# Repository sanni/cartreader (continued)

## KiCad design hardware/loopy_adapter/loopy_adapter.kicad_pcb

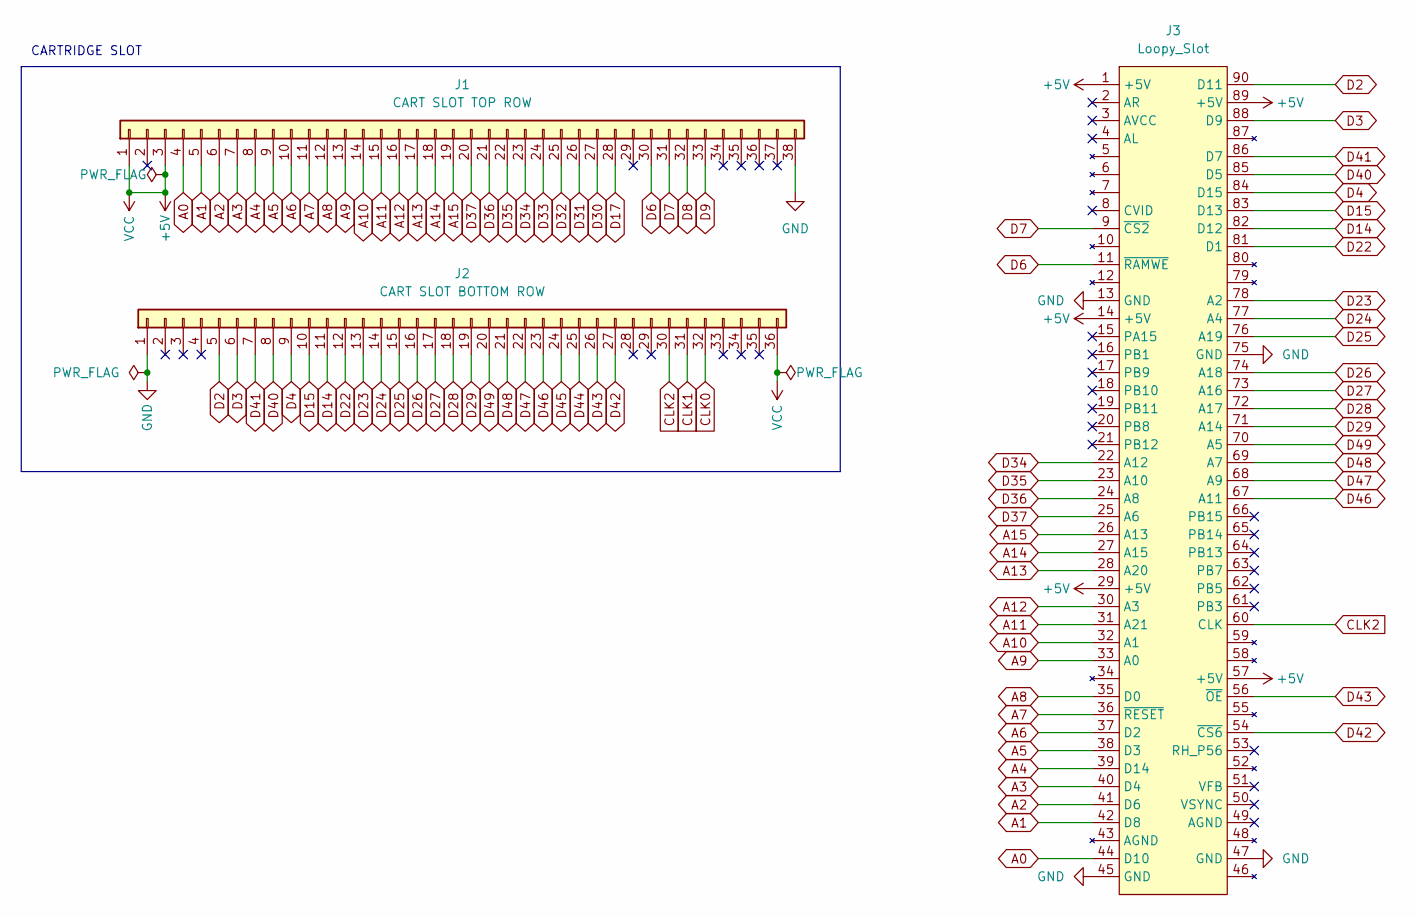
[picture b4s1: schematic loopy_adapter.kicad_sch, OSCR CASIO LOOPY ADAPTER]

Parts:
J1: CART SLOT TOP ROW; PinSocket_1x38_P2.54mm_Vertical
J2: CART SLOT BOTTOM ROW; PinSocket_1x36_P2.54mm_Vertical
J3: Loopy_Slot

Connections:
+5V: J1.1, J1.3, J2.36, J3.1 (+5V), J3.14 (+5V), J3.29 (+5V), J3.57 (+5V), J3.89 (+5V)
A0: J1.4, J3.44 (D10)
A1: J1.5, J3.42 (D8)
A2: J1.6, J3.41 (D6)
A3: J1.7, J3.40 (D4)
A4: J1.8, J3.39 (D14)
A5: J1.9, J3.38 (D3)
A6: J1.10, J3.37 (D2)
A7: J1.11, J3.36 (~RESET)
A8: J1.12, J3.35 (D0)
A9: J1.13, J3.33 (A0)
A10: J1.14, J3.32 (A1)
A11: J1.15, J3.31 (A21)
A12: J1.16, J3.30 (A3)
A13: J1.17, J3.28 (A20)
A14: J1.18, J3.27 (A15)
A15: J1.19, J3.26 (A13)
CLK0: J2.32
CLK1: J2.31
CLK2: J2.30, J3.60 (CLK)
D2: J2.5, J3.90 (D11)
D3: J2.6, J3.88 (D9)
D4: J2.9, J3.84 (D15)
D6: J1.30, J3.11 (~RAMWE)
D7: J1.31, J3.9 (~CS2)
D8: J1.32
D9: J1.33
D14: J2.11, J3.82 (D12)
D15: J2.10, J3.83 (D13)
D17: J1.28
D22: J2.12, J3.81 (D1)
D23: J2.13, J3.78 (A2)
D24: J2.14, J3.77 (A4)
D25: J2.15, J3.76 (A19)
D26: J2.16, J3.74 (A18)
D27: J2.17, J3.73 (A16)
D28: J2.18, J3.72 (A17)
D29: J2.19, J3.71 (A14)
D30: J1.27
D31: J1.26
D32: J1.25
D33: J1.24
D34: J1.23, J3.22 (A12)
D35: J1.22, J3.23 (A10)
D36: J1.21, J3.24 (A8)
D37: J1.20, J3.25 (A6)
D40: J2.8, J3.85 (D5)
D41: J2.7, J3.86 (D7)
D42: J2.27, J3.54 (~CS6)
D43: J2.26, J3.56 (~OE)
D44: J2.25
D45: J2.24
D46: J2.23, J3.67 (A11)
D47: J2.22, J3.68 (A9)
D48: J2.21, J3.69 (A7)
D49: J2.20, J3.70 (A5)
GND: J1.38, J2.1, J3.13 (GND), J3.45 (GND), J3.47 (GND), J3.75 (GND)

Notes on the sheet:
CARTRIDGE SLOT

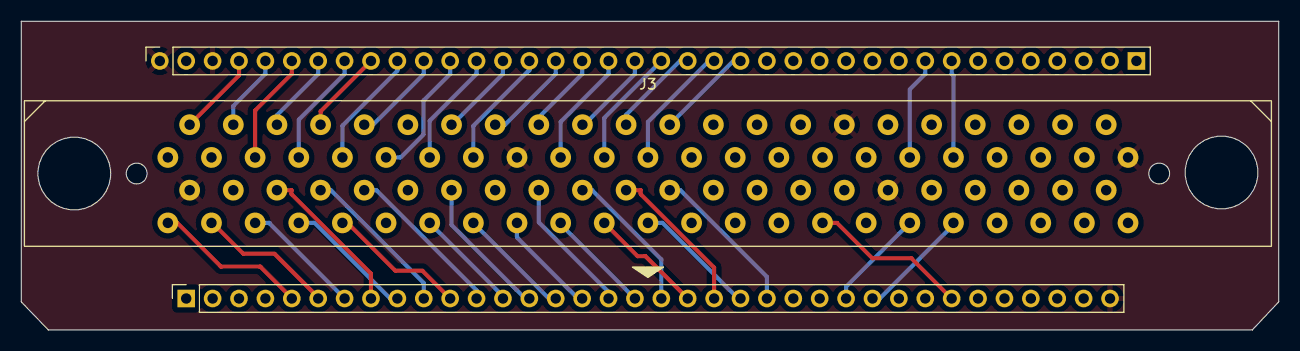
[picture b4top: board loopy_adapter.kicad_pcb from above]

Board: 2 copper layers, 121.0 x 29.7 mm, 3 parts (0 on the bottom side), 46 nets.

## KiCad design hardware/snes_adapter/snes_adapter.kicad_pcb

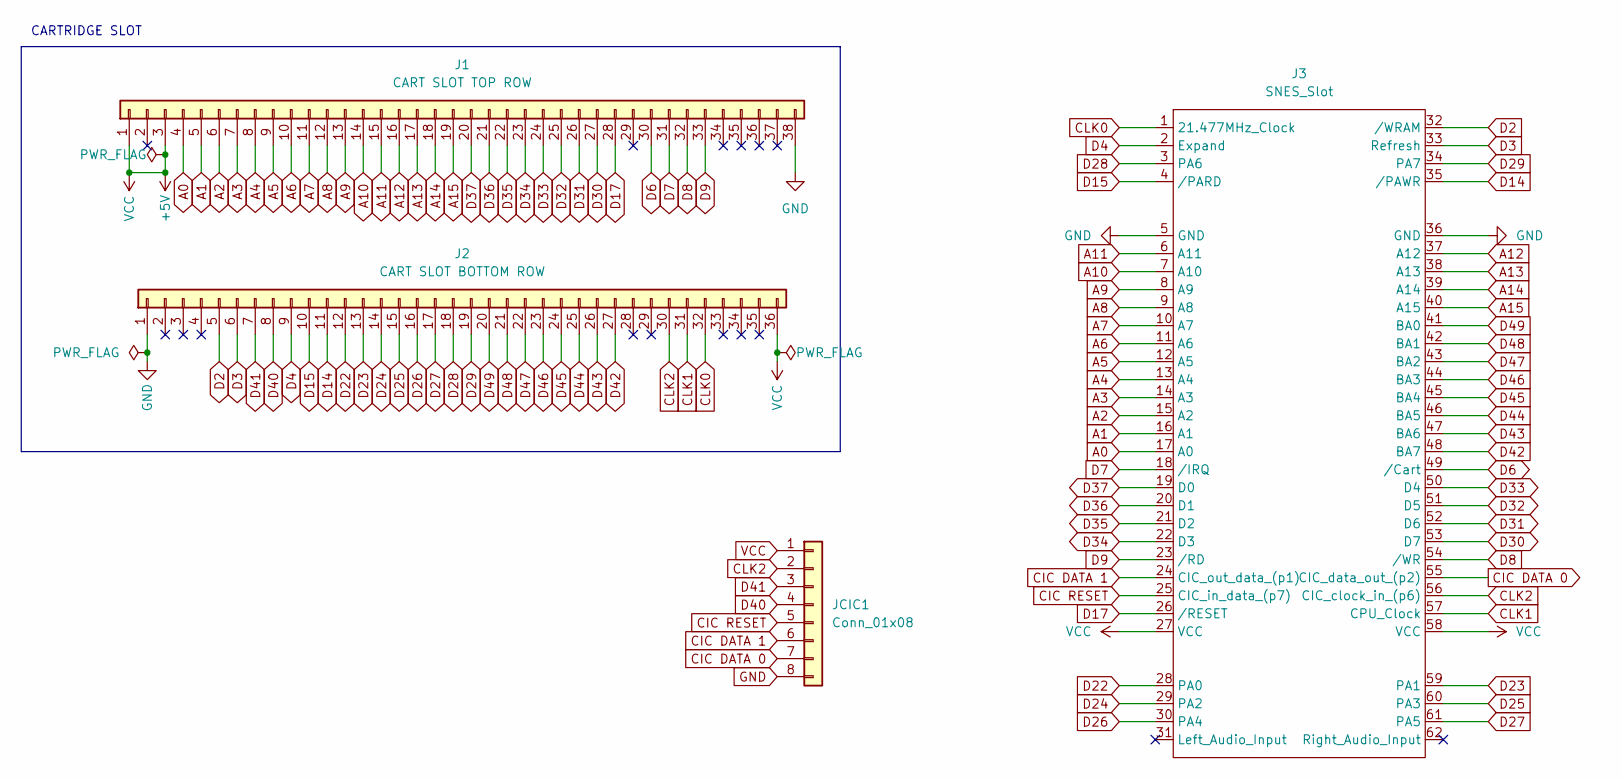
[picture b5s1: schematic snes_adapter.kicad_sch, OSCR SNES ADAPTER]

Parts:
J1: CART SLOT TOP ROW; PinSocket_1x38_P2.54mm_Vertical
J2: CART SLOT BOTTOM ROW; PinSocket_1x36_P2.54mm_Vertical
J3: SNES_Slot
JCIC1: Conn_01x08

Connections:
A0: J1.4, J3.17 (A0)
A1: J1.5, J3.16 (A1)
A2: J1.6, J3.15 (A2)
A3: J1.7, J3.14 (A3)
A4: J1.8, J3.13 (A4)
A5: J1.9, J3.12 (A5)
A6: J1.10, J3.11 (A6)
A7: J1.11, J3.10 (A7)
A8: J1.12, J3.9 (A8)
A9: J1.13, J3.8 (A9)
A10: J1.14, J3.7 (A10)
A11: J1.15, J3.6 (A11)
A12: J1.16, J3.37 (A12)
A13: J1.17, J3.38 (A13)
A14: J1.18, J3.39 (A14)
A15: J1.19, J3.40 (A15)
CIC DATA 0: J3.55 (CIC_data_out_(p2)), JCIC1.7
CIC DATA 1: J3.24 (CIC_out_data_(p1)), JCIC1.6
CIC RESET: J3.25 (CIC_in_data_(p7)), JCIC1.5
CLK0: J2.32, J3.1 (21.477MHz_Clock)
CLK1: J2.31, J3.57 (CPU_Clock)
CLK2: J2.30, J3.56 (CIC_clock_in_(p6)), JCIC1.2
D2: J2.5, J3.32 (/WRAM)
D3: J2.6, J3.33 (Refresh)
D4: J2.9, J3.2 (Expand)
D6: J1.30, J3.49 (/Cart)
D7: J1.31, J3.18 (/IRQ)
D8: J1.32, J3.54 (/WR)
D9: J1.33, J3.23 (/RD)
D14: J2.11, J3.35 (/PAWR)
D15: J2.10, J3.4 (/PARD)
D17: J1.28, J3.26 (/RESET)
D22: J2.12, J3.28 (PA0)
D23: J2.13, J3.59 (PA1)
D24: J2.14, J3.29 (PA2)
D25: J2.15, J3.60 (PA3)
D26: J2.16, J3.30 (PA4)
D27: J2.17, J3.61 (PA5)
D28: J2.18, J3.3 (PA6)
D29: J2.19, J3.34 (PA7)
D30: J1.27, J3.53 (D7)
D31: J1.26, J3.52 (D6)
D32: J1.25, J3.51 (D5)
D33: J1.24, J3.50 (D4)
D34: J1.23, J3.22 (D3)
D35: J1.22, J3.21 (D2)
D36: J1.21, J3.20 (D1)
D37: J1.20, J3.19 (D0)
D40: J2.8, JCIC1.4
D41: J2.7, JCIC1.3
D42: J2.27, J3.48 (BA7)
D43: J2.26, J3.47 (BA6)
D44: J2.25, J3.46 (BA5)
D45: J2.24, J3.45 (BA4)
D46: J2.23, J3.44 (BA3)
D47: J2.22, J3.43 (BA2)
D48: J2.21, J3.42 (BA1)
D49: J2.20, J3.41 (BA0)
GND: J1.38, J2.1, J3.5 (GND), J3.36 (GND), JCIC1.8
VCC: J1.1, J1.3, J2.36, J3.27 (VCC), J3.58 (VCC), JCIC1.1

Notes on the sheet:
CARTRIDGE SLOT

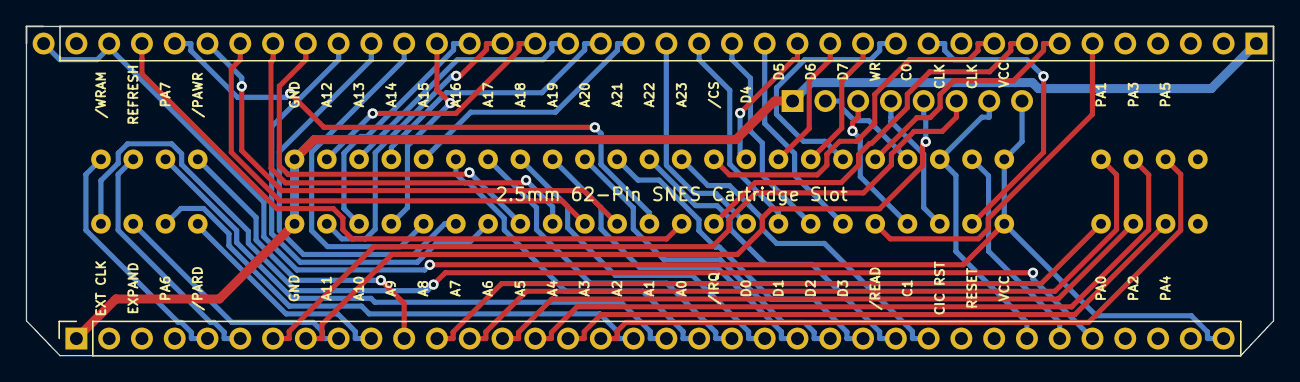
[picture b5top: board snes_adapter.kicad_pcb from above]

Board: 2 copper layers, 96.6 x 25.5 mm, 4 parts (1 on the bottom side), 60 nets.

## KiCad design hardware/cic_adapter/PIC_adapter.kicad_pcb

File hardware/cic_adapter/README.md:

### Important: The CIC adapters are completely untested and still a work-in-progress, so the PCB files might contain errors or not work at all.    

##

The D411_F411_adapter is for using the original CIC chip either out of a cartridge(D411) or out of a SNES console(F411). They will be region locked and you can only dump SA1 games from the region of the CIC chip. Furthermore it has not been tested if this works at all, so right now it's just an unproven idea to save people the trouble of programming a PIC microcontroller.    

##

The PIC_adapter is for using either the PIC12F629 DIP or SMD(flashed with snescic-lock-resync.hex) or PIC16F630 DIP(flashed with supercic-lock_p16f630.hex) microcontrollers. They are region-free so they can dump SA1 cartridges from any country.     

Hexfiles:     
- [snescic-lock-resync.hex](https://github.com/mrehkopf/sd2snes/tree/develop/cic)    
- [supercic-lock_p16f630.hex](https://sd2snes.de/blog/cool-stuff/supercic)      

More Info:   
- [Flashing the snesCIC](https://github.com/sanni/cartreader/wiki/Flashing-the-snesCIC)

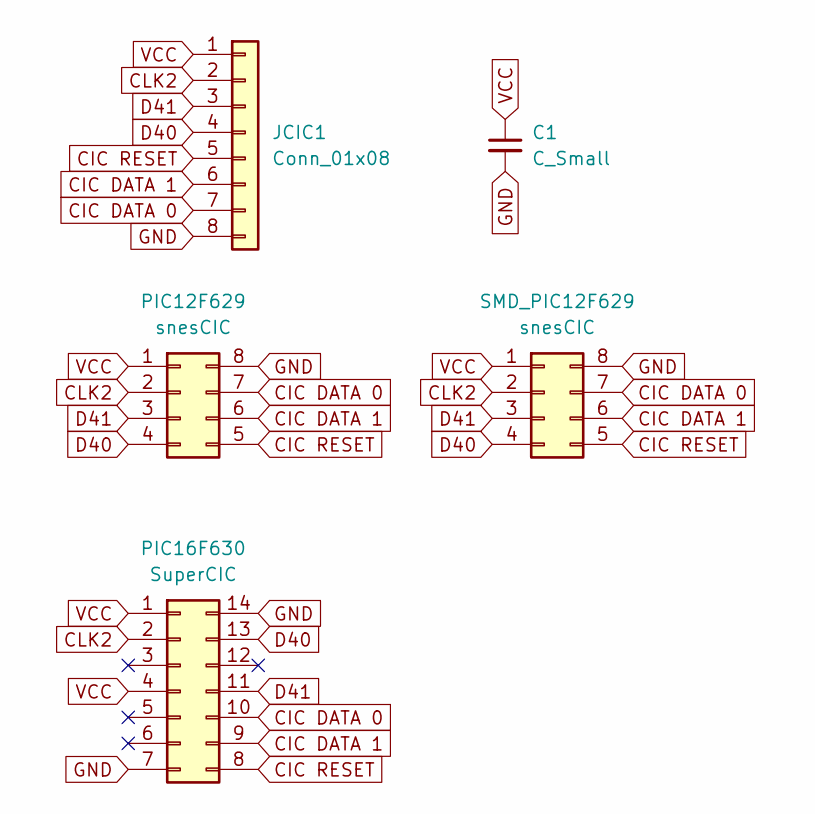
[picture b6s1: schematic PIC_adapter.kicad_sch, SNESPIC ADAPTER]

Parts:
C1: C_Small
JCIC1: Conn_01x08
PIC12F629: snesCIC
PIC16F630: SuperCIC
SMD_PIC12F629: snesCIC

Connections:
CIC DATA 0: JCIC1.7, PIC12F629.7, PIC16F630.10, SMD_PIC12F629.7
CIC DATA 1: JCIC1.6, PIC12F629.6, PIC16F630.9, SMD_PIC12F629.6
CIC RESET: JCIC1.5, PIC12F629.5, PIC16F630.8, SMD_PIC12F629.5
CLK2: JCIC1.2, PIC12F629.2, PIC16F630.2, SMD_PIC12F629.2
D40: JCIC1.4, PIC12F629.4, PIC16F630.13, SMD_PIC12F629.4
D41: JCIC1.3, PIC12F629.3, PIC16F630.11, SMD_PIC12F629.3
GND: C1.2, JCIC1.8, PIC12F629.8, PIC16F630.7, PIC16F630.14, SMD_PIC12F629.8
VCC: C1.1, JCIC1.1, PIC12F629.1, PIC16F630.1, PIC16F630.4, SMD_PIC12F629.1

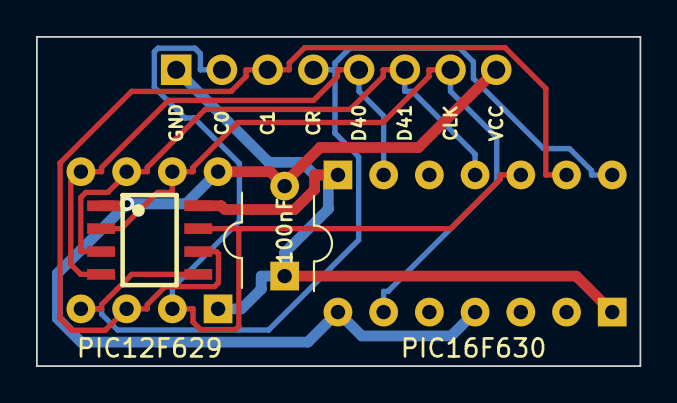
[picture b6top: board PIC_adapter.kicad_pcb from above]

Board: 2 copper layers, 33.5 x 18.3 mm, 5 parts (1 on the bottom side), 8 nets.

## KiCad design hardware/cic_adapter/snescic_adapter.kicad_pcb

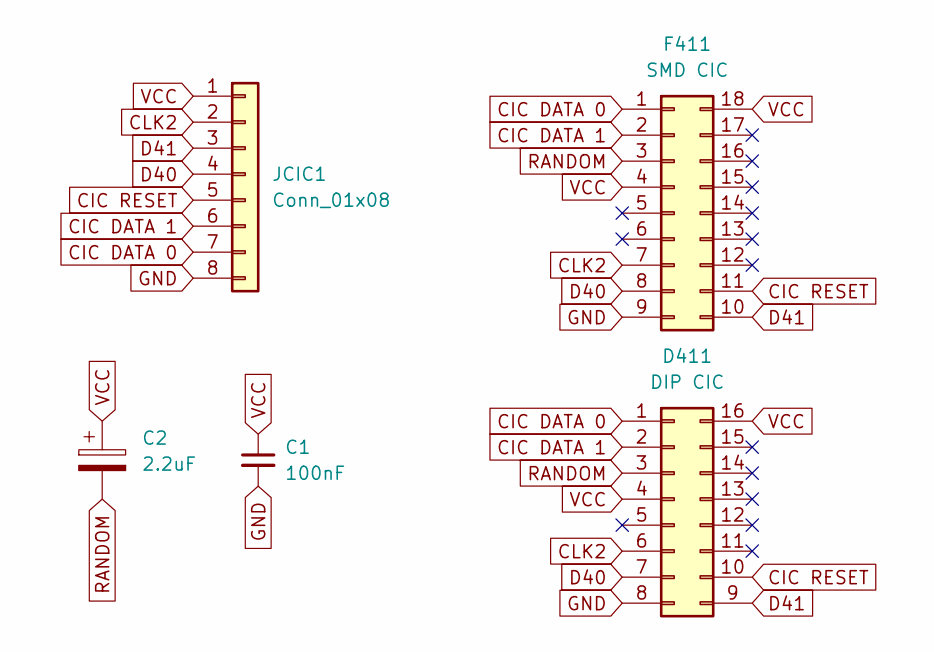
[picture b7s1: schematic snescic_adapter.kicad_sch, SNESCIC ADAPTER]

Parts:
C1: 100nF
C2: 2.2uF
D411: DIP CIC
F411: SMD CIC
JCIC1: Conn_01x08

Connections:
CIC DATA 0: D411.1, F411.1, JCIC1.7
CIC DATA 1: D411.2, F411.2, JCIC1.6
CIC RESET: D411.10, F411.11, JCIC1.5
CLK2: D411.6, F411.7, JCIC1.2
D40: D411.7, F411.8, JCIC1.4
D41: D411.9, F411.10, JCIC1.3
GND: C1.2, D411.8, F411.9, JCIC1.8
RANDOM: C2.2, D411.3, F411.3
VCC: C1.1, C2.1, D411.4, D411.16, F411.4, F411.18, JCIC1.1

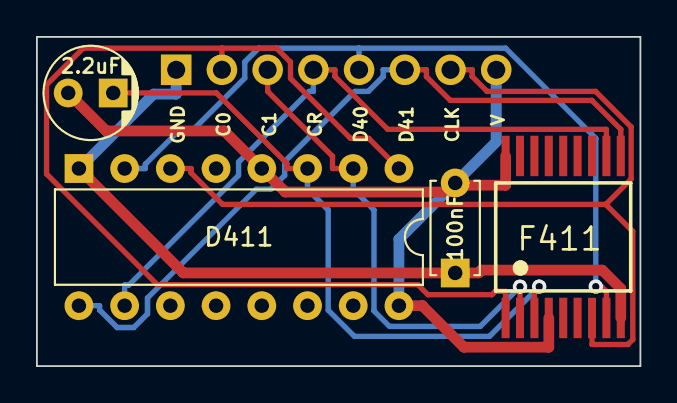
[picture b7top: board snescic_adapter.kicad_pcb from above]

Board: 2 copper layers, 33.5 x 18.3 mm, 5 parts (1 on the bottom side), 9 nets.

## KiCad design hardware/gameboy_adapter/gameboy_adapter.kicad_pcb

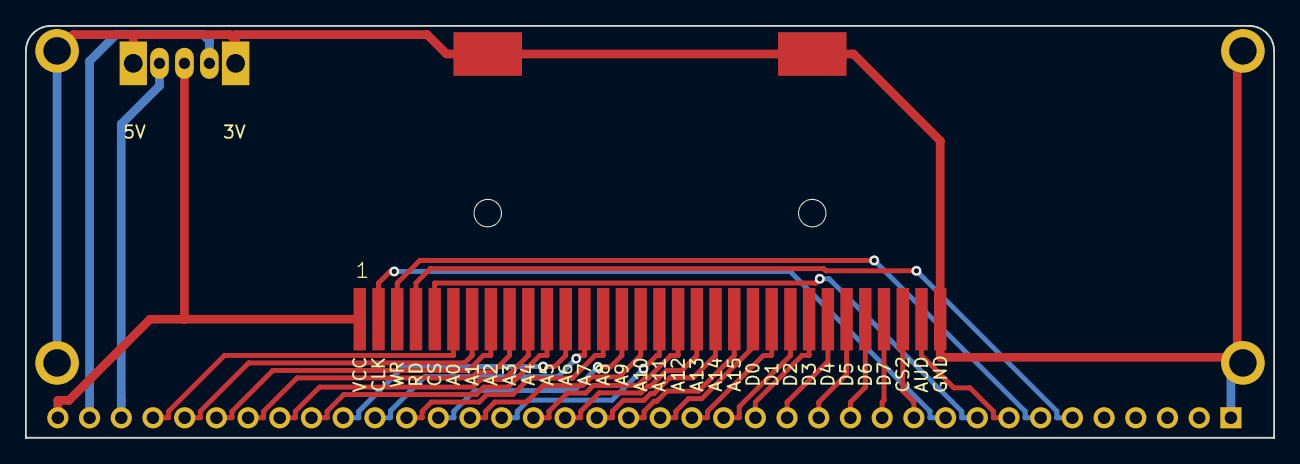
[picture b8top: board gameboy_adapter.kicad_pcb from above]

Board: 2 copper layers, 100.0 x 33.0 mm, 7 parts (0 on the bottom side), 34 nets.

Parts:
J1: CART SLOT TOP ROW; PinSocket_1x38_P2.54mm_Vertical
J2: GBA_Slot; GBA-SLOT-B
M2_1, M2_2, M2_3, M2_10: Screw_Terminal_01x01; MountingHole_2.2mm_M2_ISO7380_Pad
SW1: SW_SPDT; SW_CuK_OS102011MA1QN1_SPDT_Angled

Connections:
+3V3: J1.2, SW1.1 (A)
+5V: J1.3, SW1.3 (C)
A0: J1.4, J2.6 (AD0)
A1: J1.5, J2.7 (AD1)
A2: J1.6, J2.8 (AD2)
A3: J1.7, J2.9 (AD3)
A4: J1.8, J2.10 (AD4)
A5: J1.9, J2.11 (AD5)
A6: J1.10, J2.12 (AD6)
A7: J1.11, J2.13 (AD7)
A8: J1.12, J2.14 (AD8)
A9: J1.13, J2.15 (AD9)
A10: J1.14, J2.16 (AD10)
A11: J1.15, J2.17 (AD11)
A12: J1.16, J2.18 (AD12)
A13: J1.17, J2.19 (AD13)
A14: J1.18, J2.20 (AD14)
A15: J1.19, J2.21 (AD15)
D6: J1.30, J2.5 (CS1)
D7: J1.31, J2.31 (AUD_IRQ)
D8: J1.32, J2.3 (WR)
D9: J1.33, J2.4 (RD)
D16: J1.29, J2.2 (CLK)
D17: J1.28, J2.30 (RST_CS2)
D30: J1.27, J2.29 (D7_A23)
D31: J1.26, J2.28 (D6_A22)
D32: J1.25, J2.27 (D5_A21)
D33: J1.24, J2.26 (D4_A20)
D34: J1.23, J2.25 (D3_A19)
D35: J1.22, J2.24 (D2_A18)
D36: J1.21, J2.23 (D1_A17)
D37: J1.20, J2.22 (D0_A16)
GND: J1.38, J2.32 (GND), J2.SHIELD_3, J2.SHIELD_4, M2_1.1, M2_2.1, M2_3.1, M2_10.1
VCC: J1.1, J2.1 (VCC), SW1.2 (B)

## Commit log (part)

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2024-04-22 remove some duplicate printing code and declare more global text strings
2024-04-24 replace cart select code with code used in NES, COLV, INTV
2024-04-27 replace 2600 cart selection code with code used in NES, COLV & INTV
2024-04-27 Update c64cart.txt
    Updated to work with C64.ino that fixes Issue #902
2024-04-28 replace C64 cart selection code with code used in NES, COLV & INTV
2024-04-28 fix ordering in 7800.txt
2024-04-28 fix formatting of newly added documentation
2024-04-29 add 5200 and arccart section to README.md
2024-05-01 replace FAIRCHILD, ODY2, MSX and VECTREX cart selection code with code used in NES, COLV & INTV. Define "Database not found" in OSCR.cpp
2024-05-01 remove duplicate CRC printing and calculation function
2024-05-01 remove duplicate code in printing CRC
2024-05-03 remove duplicate string literals
2024-05-03 fix signed/unsigned warning
2024-05-03 Add support for mapper 3E, 32K ROM 32K RAM Tigervision
2024-05-07 fix 2600 mapper selection for Serial
2024-05-07 Fixed (added) missing FS() macro on some FSTRING constants
    This was causing two symptoms/bugs:
    * OSCR_LOG.txt was being spammed with random data.
    * The size of OSCR_LOG.txt would get so big that copying the log would take a long time, possibly minutes. Oftentimes this caused the display to appear to hang after searching for the CRC (after "->"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
    If using the global log and a version of master since e61ac414d89556c941f0b8ca76e5d7d6684037f0 you should delete OSCR_LOG.txt from your SD card as it will likely be very large and continue to cause d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
2024-05-10 add serial printing to print instructions
2024-05-11 define "File doesn't exist" in OSCR.cpp/h
2024-05-12 reduce duplicate code by parameterise ROML/ROMH
2024-05-12 remove duplicate code for 2600 3E & 3F mapper
2024-05-12 use constant for "Saving to" instead declare the string several times
2024-05-20 remove duplicate code to open file for verfication
2024-05-20 remove duplicate code to write Flash Command
2024-05-24 support mapper > 255, implement mapper 446 submapper 0&1 - thanks to NewRisingSun for support, fix iNES2.0 mapper parsing of byte 8
2024-05-25 add option to clear display and remove duplicate code
2024-05-26 add common function to open create folder, print message and open file. Remove duplicate code
2024-05-28 define more commonly used string in OSCR and reuse them
2024-05-30 reuse code to write NES maker command
2024-05-30 reuse n64 flashrom Xplorer command sequence
2024-06-02 Add checks for unsafe configurations
    * Fixes #929
    * Updated `ci.yml` to define `GITHUB_CI`
    * Compilation will now error if VSELECT is enabled on hardware versions that don't support it (any version other than HW5).
    * HW4 and SERIAL might work but are untested. The error message for these versions reflects this.
    * Erroring when unsafe configurations are defined can be overridden by defining `ALLOW_UNSAFE_CONFIG` which will throw a warning instead.
    * This should only be done if trying to implement or test on a currently unsupported platform.
2024-06-03 reuse command sequence for GB
2024-06-10 Fix compilation errors when the FLASH core is enabled without FLASH16
    Commit References:
    * a32c6b3bfff066b04d81faea0e578b80cb4a3108 - Added ATTENTION_3_3V flash string but placed the definition inside a FLASH16 ifdef.
    * 4d000418a8f4e4a29297f83e30922100da7b21f5 - Added use of writeWord_Flash to FLASH8 without removing the FLASH16 ifdef around it.
2024-06-13 Add option to force ROM size for MD carts
2024-06-15 replace duplicate error string "Can't open file"
2024-06-16 define common string "Select file"
2024-06-26 SNES: Add 2x2MB flash to CFI (thx to MouseBiteLabs)
2024-06-27 Fix verifyFlash()
2024-06-29 reuse common string "ROM Size: "
2024-06-29 Disable SRAM when flashing 2x2MB repro
2024-06-30 Cleaning up debug stuff
2024-06-30 Always disable SRAM when flashing any hirom repros
2024-06-30 Fix reading Bahamut Lagoon English Translation SRAM (thx to Cowboyjunkie)
    https://github.com/sanni/cartreader/issues/917
2024-06-30 Alternate fix
2024-07-02 Fix color cycling when idle
2024-07-05 13.5 Fix SFM flash menu
    https://github.com/sanni/cartreader/issues/980
2024-07-07 Cherry-picking firmware changes only for Lynx support
    Updating header comments
    Better blocksize detection, cleanups
2024-07-07 Further optimize detection, combine loops
2024-07-08 GBA: Add basic support for F0088H0 flash
    No bank switching yet so ROM limited to 16MB.
    Uses flash commands found [here](https://github.com/lesserkuma/FlashGBX/blob/master/FlashGBX/config/fc_AGB_6600M0U0BE.txt)
2024-07-09 GBA: Fix Blankcheck function
2024-07-12 GBA: Add option to dump F0088H0 repro
2024-07-19 Flash: Add progress bar to read/verify/blankcheck flashrom
2024-07-24 add Chess to 2600. This is a variant of Video Chess
2024-07-29 SMS Updates
    1. SMS cart size detection algorithm is updated based on bank count instead of multiples of detected cart size from the header.
    2. SMS cart size detection is only invoked if the "TMR SEGA" header is parsed for non-JP carts.
    3. Manual selection of ROM size is now present in the SMS/GG menus to allow for manual override as detection algorithm does not work correctly for Cloud Master and Penguin Land US SMS carts.
    4. SG-1000 Operation menu now allows for reset instead of relying on a power cycle.
2024-07-31 Output clock signal during self test
2024-08-01 Atari 5200 Updates
    1. Added CRC database lookup for ROM dump validation and file renaming
    2. Added delays to improve successful ROM dumping. Especially helps with
    2-chip ROMs
    3. Fixed database mapper config for Star Trek (not a 2-chip ROM)
2024-08-04 Adds flash cartridge support to Atari Lynx firmware
2024-08-07 Add new options to SNES CFI repro menu
2024-08-11 Change N64 timings
    Seems to more reliable read SRAM with some delays removed.
2024-08-13 Support Flash repro A29040B
2024-08-15 Remove "Rotate to Change Press to Select" spam from log file
2024-08-16 Disable N64 controller test by default
2024-08-16 Fix compiler warnings/errors
2024-08-16 Remove more co-dependencies
2024-08-28 Fix/cleanup the VSELECT Module project files
    * Fixed the field name for the LCSC part number so the BOM exports with the part numbers.
    * Removed the test points from the schematic as they are no longer needed.
    * Added notes for setting the ILIM resistor to the schematic.
    * Added an image of the PCB and PDF of the schematic.
    Note: The PCB itself didn't change, so it is still Rev 3.
2024-08-28 Update NES.ino - fix mapper 80+82
    fix mapper 80+82
2024-09-11 Add writing MD FlashKit with S29GL064N
2024-09-12 Release CPS3 OSCR Adapter commit
2024-09-13 Add support for 39F040 to flash programmer
2024-09-13 Update lynx.txt
    Fix title names
2024-09-15 GB: Only trigger audio and not WR on flash cart with audio as WE, add 39SF cart without MBC
2024-09-20 Add 39SF020 and 39SF010 to flashrom programmer
2024-10-03 add 2600 games "Ente und der Wolf, Der", "Feuerwehr im Einsatz" & "Moderne Ritter, Der"
2024-11-05 docs: update README.md
    Github -> GitHub
2024-11-09 LEAP.ino : fixed dumping and typos
    LEAP.ino : fixed dumping and typos
2024-11-14 Update NES.ino : added mapper 268 submapper 0
    Update NES.ino : added mapper 268 submapper 0
2024-11-27 Fix `printInstructions()` overriding `dont_log` state
2024-12-07 add Berzerk and Space Duel to 7800
2024-12-15 Update NES.ino
    fix mapper 52
2024-12-21 Update NES.ino
    - RAM dump extension changed from .bin to .sav for direct use with emulators (see https://github.com/sanni/cartreader/discussions/1049)
    - regrouped scripts for MMC3-based mappers
    - regrouped scripts for CxROM-like mappers
    - regrouped scripts for BxROM-like mappers
    - added support for 268 submapper 1
2024-12-23 Update Cart_Reader.ino
    - Remove incomingByte global variable, mark all uses as local
    variables. This leads to a tiny (yet measurable) decrease in global
    variable use, and no change in sketch memory use. Of course, the
    variable now resides in the stack, but only while the functions using
    it exist, which isn't always.
2024-12-23 Update GB.ino
    - Move shared GB port initialization into its own function
2024-12-26 Update NES.ino
    Modified Mapper 226 to use pulsing M2 code (BMC Super 42-in-1, 76-in-1, et al.).
    Added Mapper 233 which requires power cycling the cart reader to switch between the two PRG chips (BMC 22-in-1/20-in-1 (42-in-1)).
2025-01-01 support "Bentley Bear's Crystal Quest" and "Bounty Bob Strikes Back!"
2025-01-01 Update nes.txt - sync'd with no-intro + sorted by release type
    Update nes.txt - sync'd with no-intro + sorted by release type instead of alphabetical: Licensed > Unlicensed > Pirate > Aftermarket. that will speed up things for the vast majority of users
2025-01-07 Fix offset address for mapper 24/26/78
2025-01-18 Update NES.ino
    - started mappers list cleanup
    - added mappers 12, 29, 115, 117, 120, 122, 125, 144, 182, 248, 532
2025-01-19 Update nes.txt
    sync'd with no-intro, reverted to default (alphabetical) order because it breaks game selection by name otherwise
2025-01-21 Update NES.ino
    Updated Mapper 45 to handle Dynavision 101 Games and 106 Games carts (4096K PRG). Added Mappers 237, 289, 319, and 332. Mappers 289 and 332 need pulsing M2 code to dump properly.
2025-01-22 Update NES.ino
    - mapper 268 typo fix
2025-01-24 Update NES.ino
    - added mapper 221, 288, 290
2025-01-26 Update NES.ino
    - added mappers 224, 396, 422, 534
    - added placeholders for 268 submappers 2-11 at fake numbers 995-999
2025-02-01 Update NES.ino
    - added mappers 272, 380, 519
2025-02-16 Update NES.ino
    Updated Mapper 178. Added Mapper 314. Mapper 314 needs pulsing M2 for register settings.
2025-02-26 Update VBOY.ino
    Add manual Rom size selection menu for unknown carts.
    Add 64KB Rom support.
    Add new serials to supported titles list.
2025-03-30 add DFSC Penult
2025-03-31 remove my HW define so automatic pull request may work
2025-04-18 add several Quelle Atari 2600 games
2025-04-25 Update Config.h - disabled A2600 that was ON by default
    disabled A2600 that was ON by default
2025-05-19 Adds support for M29F080 flash to PCE, tested
2025-05-22 Fix error when entering empty folder
2025-05-31 Remove unnecessary logs
2025-06-02 Add config tool for portable release
    This replaces that three *.bat files that are currently in the portable release.
2025-06-02 Remove compiled exe
2025-06-02 Start Arduino IDE with the Cart_Reader sketch already selected
2025-06-03 Fix script not closing if there is no error.
2025-06-13 Update NES.ino - added mapper 312
    added mapper 312 for Kaiser's Highway Star (untested)
2025-06-19 Update monthly_release.yml - Add 7zip archive
2025-06-19 Prevent arduino-cli from writing to \AppData\Local
2025-06-19 Fix avrdude timeout on old PC
2025-07-08 Update SNES.ino - Fix crashing menu when enabling Clock Calibration
2025-07-29 Re-structure GB repro menu & fix dumping GB ROM with no name in header
    MBC1 option probably not working yet
2025-08-07 Update NES.ino - fix mapper 380
    mapper 380 needs M2 pulse, tested working
2025-08-14 Use F() in MD.ino CFI code.
2025-08-18 Identify SRAM chip when flashing Genesis CFI.
    In a board with 1 flash chip and SRAM, the SRAM is always enabled so attempting
    to detect it as CFI will fail.
    This commit adds some simple code that attempts to modify address 0x0 of the
    chip to detect if the chip is ROM or SRAM. If the value changes upon writing to
    it, it will assume it's SRAM and ignore it when flashing.
2025-08-18 N64: fix default cartsize for unknown cart
2025-08-23 Bump version to V15.2 after bi-monthly release
2025-09-05 Add support for Genesis 29F800 under CFI.
    The 29F800 supports CFI commands as is except for the ID command, so this adds
    custom code to identify it.
    Rewrote the identifyCFI function a bit to make it more readable.
2025-09-07 Sort GBA database by cart ID and fix nulled out cart ID
2025-09-10 Update NES.ino - fix for Babel no Tou
    fix for Babel no Tou
2025-09-18 Update SMS.ino
    Comments added
2025-10-01 Bump version to V15.3 after bi-monthly release
2025-11-11 Support VSELECT on HW3
2025-12-05 Fix compile when MD/SNES are disabled
2025-12-07 add Telegames version of Bump'n'Jump
2025-12-19 NES: Fix some CRC32s
2025-12-20 Update driver URL
2025-12-20 Update AVR-GCC and Arduino CLI versions in workflow
2025-12-21 Update steps in bi-monthly release workflow
2025-12-23 Fix SD read in CRC calculation
2025-12-25 Make settings displaying optional when calling setup_7800()
2026-01-02 Redo gba database
2026-01-11 Add cleaning status dropdown to bug issue template
    Added a dropdown for cartridge pin cleaning status in bug template.
2026-03-07 [NES] Fixing incorrect control register for MMC1 CHR
    [NES] Fixing incorrect control register for MMC1 CHR, notably for SHROM and SEROM (Tetris, Dr. Mario, Boulder Dash, Anticipation and some more)
